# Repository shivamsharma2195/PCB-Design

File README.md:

This PCB design was developed for basic purpose and can be used for personal projects only

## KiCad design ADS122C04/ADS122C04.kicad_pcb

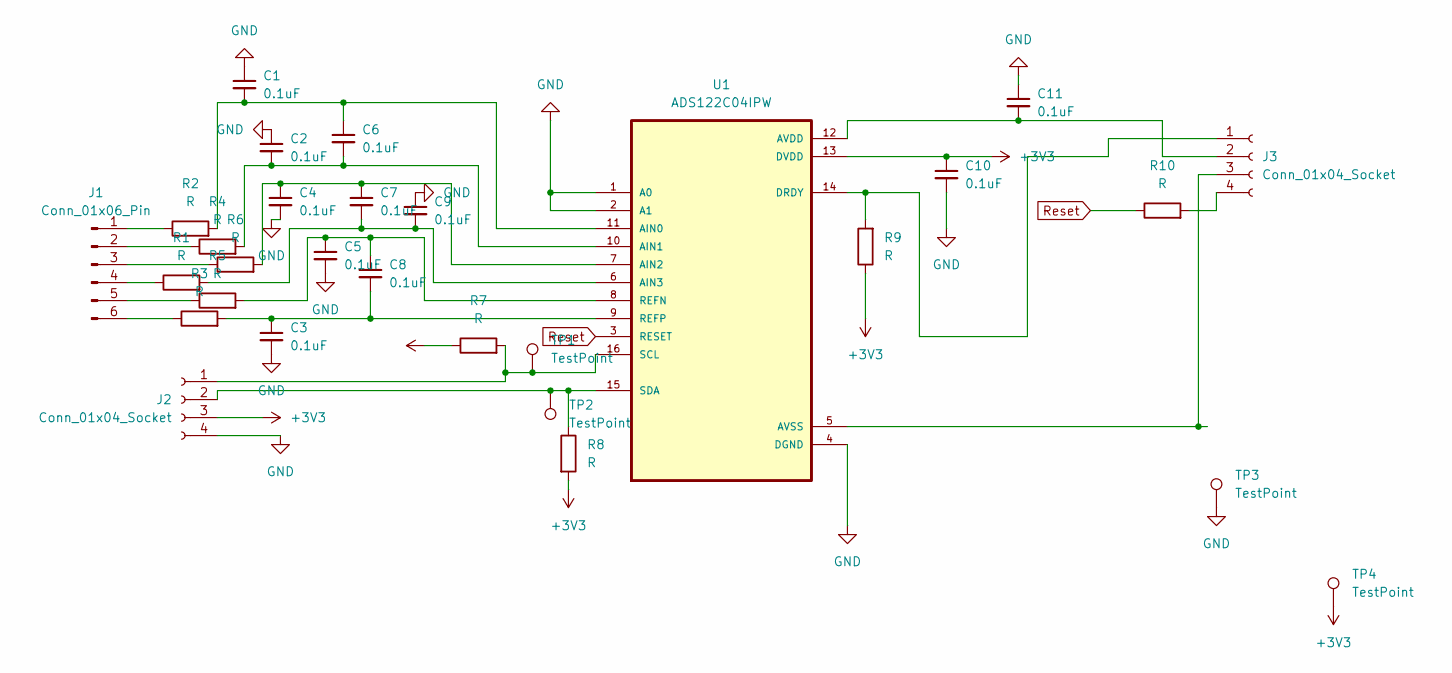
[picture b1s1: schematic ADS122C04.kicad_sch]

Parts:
C1, C2, C3, C4, C5, C6, C7, C8, C9, C10, C11: 0.1uF; C_0603_1608Metric_Pad1.08x0.95mm_HandSolder
J1: Conn_01x06_Pin; PinHeader_1x06_P2.54mm_Vertical
J2, J3: Conn_01x04_Socket; PinHeader_1x04_P2.54mm_Vertical
R1, R2, R3, R4, R5, R6, R7, R8, R9, R10: R; R_0603_1608Metric_Pad0.98x0.95mm_HandSolder
TP1, TP2, TP3, TP4: TestPoint; TestPoint_Pad_D2.0mm
U1: ADS122C04IPW; SOP65P640X120-16N

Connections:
+3V3: C10.1, J2.3, R7.1, R8.2, R9.1, TP4.1, U1.13 (DVDD)
GND: C1.1, C2.1, C3.2, C4.2, C5.2, C9.1, C10.2, C11.1, J2.4, TP3.1, U1.1 (A0), U1.2 (A1), U1.4 (DGND)
unnamed: J1.1, R2.1
unnamed: J1.2, R4.1
unnamed: J1.3, R6.1
unnamed: J1.4, R1.1
unnamed: J1.5, R5.1
unnamed: J1.6, R3.1
unnamed: J2.1, R7.2, TP1.1, U1.16 (SCL)
unnamed: J2.2, R8.1, TP2.1, U1.15 (SDA)
unnamed: J3.1, R9.2, U1.14 (DRDY)
unnamed: C11.2, J3.2, U1.12 (AVDD)
unnamed: J3.3, U1.5 (AVSS)
unnamed: J3.4, R10.2
unnamed: C1.2, C6.1, R2.2, U1.11 (AIN0)
unnamed: C2.2, C6.2, R4.2, U1.10 (AIN1)
unnamed: C4.1, C7.1, R6.2, U1.7 (AIN2)
unnamed: C7.2, C9.2, R1.2, U1.6 (AIN3)
unnamed: C5.1, C8.1, R5.2, U1.8 (REFN)
unnamed: C3.1, C8.2, R3.2, U1.9 (REFP)
Reset: R10.1, U1.3 (RESET)

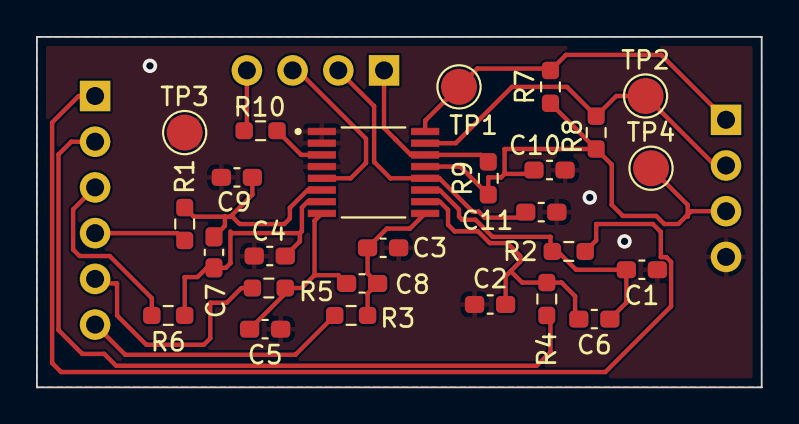
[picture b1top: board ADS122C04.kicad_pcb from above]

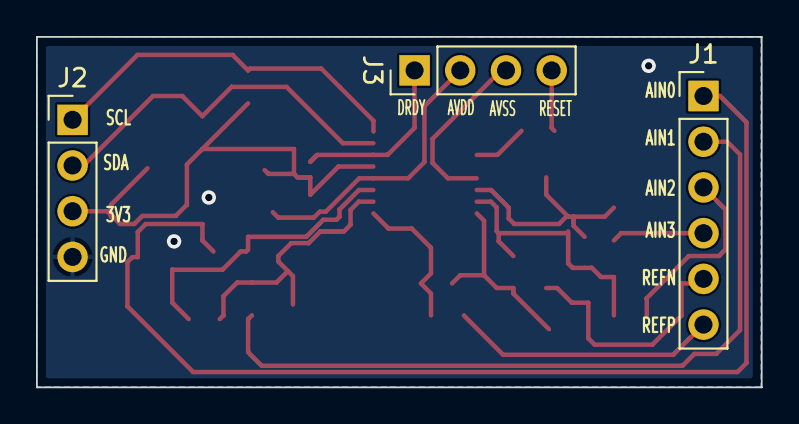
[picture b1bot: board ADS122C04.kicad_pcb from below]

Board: 2 copper layers, 40.3 x 19.5 mm, 29 parts (3 on the bottom side), 21 nets.

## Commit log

2024-07-02 ADC ADS122C04 PCB Design by Shivam
